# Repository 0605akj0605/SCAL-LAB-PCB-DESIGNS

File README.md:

# SCAL LAB: PCB Design and Hardware Integration– Automated Cooking Stove 

This repository contains PCB designs initially intended for an automated cooking stove project and the IoT hardware schematic for the proposed gas stove. Although the final implementation using a PCB was dropped, the repository includes schematic and board layouts for circuits designed during the exploration and learning phase.
Also, it contains the hardware   integrated schematic to act as a proof of concept for the proposed stove.

## 🔧 Tool Used

- [Autodesk EAGLE EDA](https://www.autodesk.com/products/eagle/overview)

## 🤝 Collaborators

Worked with **Naman Jain** and **Chiranjit Saha** to conceptualize and partially prototype an IoT-enabled automated gas stove. The system architecture included:

- Spark Plug  (to ignite the gas)
- Temperature Sensor (to monitor the flame temperature)
- MQ-7 gas sensor (for monitoring the flame)
- Servo Motor (to rotate the stove knob)
- NodeMCU for sending data to and from the IoT cloud service, ThingSpeak.
- Arduino MEGA for reading the sensor values and communicating the same with ESP32 over the UART protocol.

These components were to be integrated for automatic gas ignition and control based on environmental conditions.

## 🧩 Practice Circuit Schematic

One of the practice schematic designs is shown below:

 <!-- Make sure this path matches your repo file structure -->

## 🛠️ Skills Practiced

- PCB Schematic & Layout Design
- EAGLE Board Design Workflow
- IoT Hardware Integration
- Collaborative Design Planning

## 📌 Disclaimer

These PCB designs and hardware schematics are not part of a finalized or fabricated product, as the project was called off post the summer of 2024 after my internship duration.

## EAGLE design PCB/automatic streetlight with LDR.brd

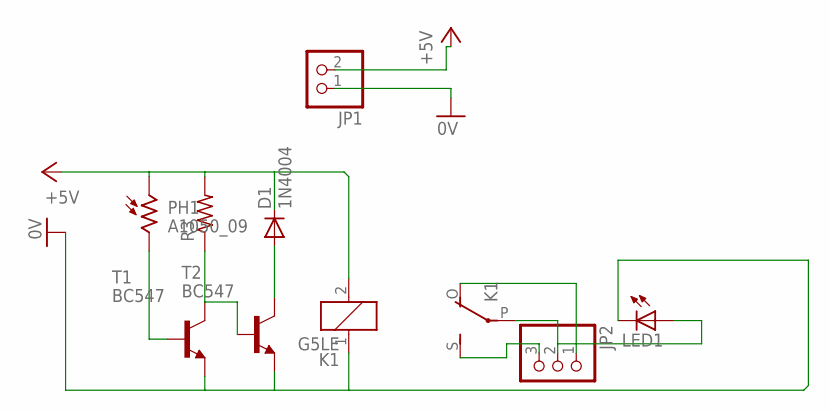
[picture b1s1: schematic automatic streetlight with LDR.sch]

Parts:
D1: 1N4004; DO41-10
JP1: PINHD-1X2; 1X02
JP2: PINHD-1X3; 1X03
K1: G5LE
LED1: LED3MM
PH1: A1050_09; T0-46-A10XX
R3: R-US_0207/10; 0207/10
T1, T2: BC547; TO92

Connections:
0V: JP1.1, K1.1, LED1.K (C), T1.1 (E), T2.1 (E)
+5V: D1.C, JP1.2, K1.2, PH1.1, R3.2
unnamed: PH1.2, T1.2 (B)
unnamed: JP2.2, K1.P, LED1.A
unnamed: JP2.1, K1.O
unnamed: JP2.3, K1.S
unnamed: R3.1, T1.3 (C), T2.2 (B)
unnamed: D1.A, T2.3 (C)

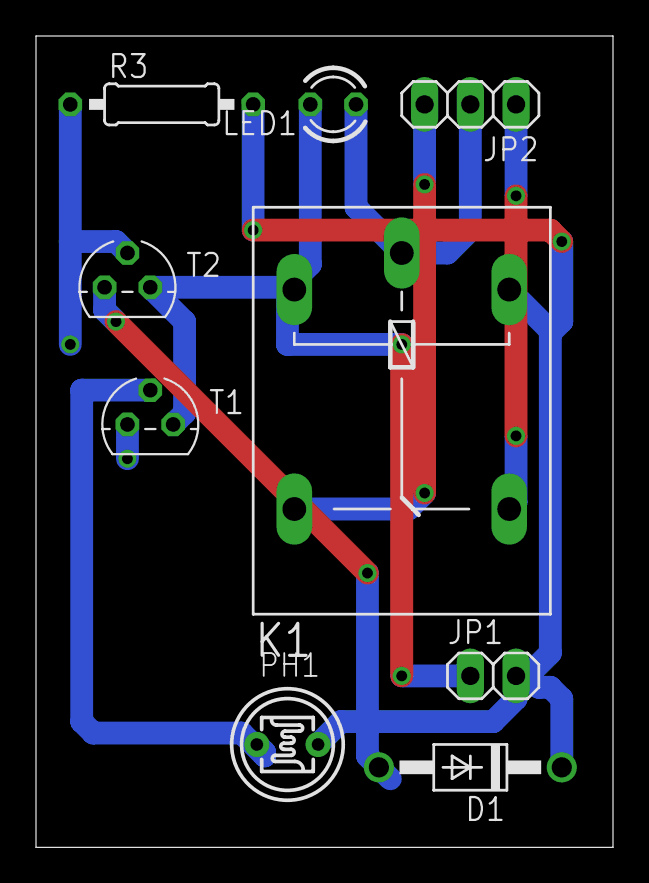
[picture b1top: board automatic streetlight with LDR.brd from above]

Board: 2 copper layers, 32.1 x 45.1 mm, 9 parts (0 on the bottom side), 8 nets.

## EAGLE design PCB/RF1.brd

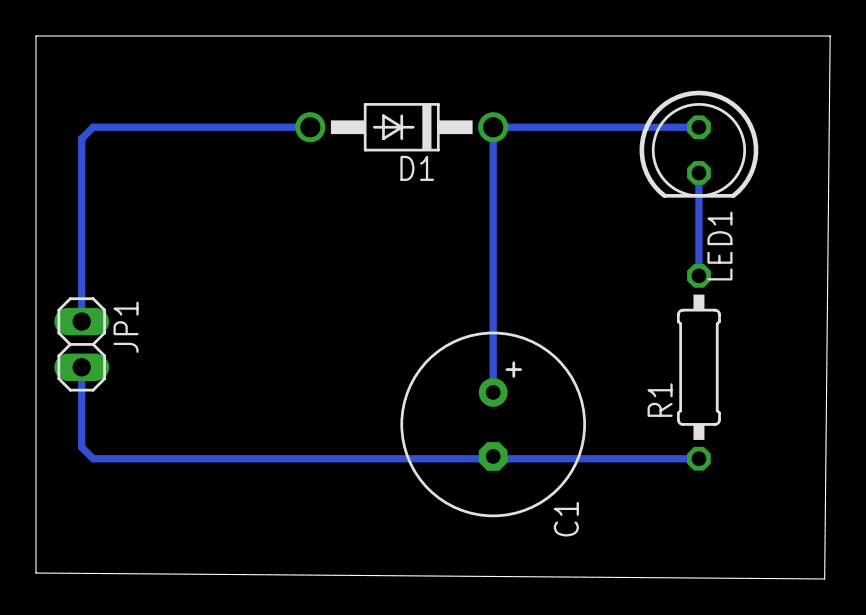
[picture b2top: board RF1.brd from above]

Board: 2 copper layers, 44.1 x 30.2 mm, 5 parts (0 on the bottom side), 4 nets.

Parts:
C1: E3,5-10
D1: 1N4004; DO41-10
JP1: 1X02
LED1: LED5MM
R1: 0207/10

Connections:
unnamed: D1.A, JP1.1
unnamed: LED1.K, R1.2
unnamed: C1.-, JP1.2, R1.1
unnamed: C1.+, D1.C, LED1.A

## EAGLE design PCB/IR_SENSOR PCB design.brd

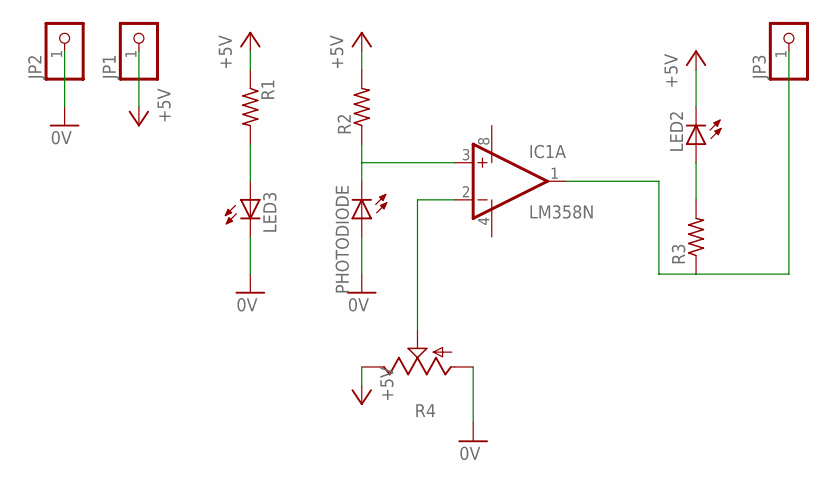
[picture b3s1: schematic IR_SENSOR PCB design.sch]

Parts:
IC1: LM358N; DIL08
JP1, JP2, JP3: PINHD-1X1; 1X01
LED2, LED3: LED3MM
PHOTODIODE: LED3MM
R1, R2, R3: R-US_0207/10; 0207/10
R4: TRIM_US-B25U; B25U

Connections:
0V: JP2.1, LED3.K (C), PHOTODIODE.A, R4.A
+5V: JP1.1, LED2.K (C), R1.1, R2.2, R4.E
unnamed: IC1.3 (+IN), PHOTODIODE.K (C), R2.1
unnamed: IC1.2 (-IN), R4.S
unnamed: LED3.A, R1.2
unnamed: LED2.A, R3.2
unnamed: IC1.1 (OUT), JP3.1, R3.1
V+: IC1.8 (V+)
V-: IC1.4 (V-)

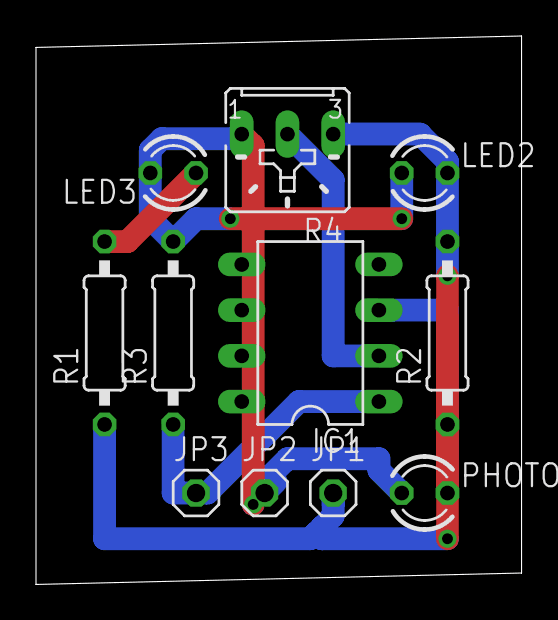
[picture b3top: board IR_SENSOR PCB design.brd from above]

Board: 2 copper layers, 27.0 x 30.5 mm, 11 parts (0 on the bottom side), 7 nets.

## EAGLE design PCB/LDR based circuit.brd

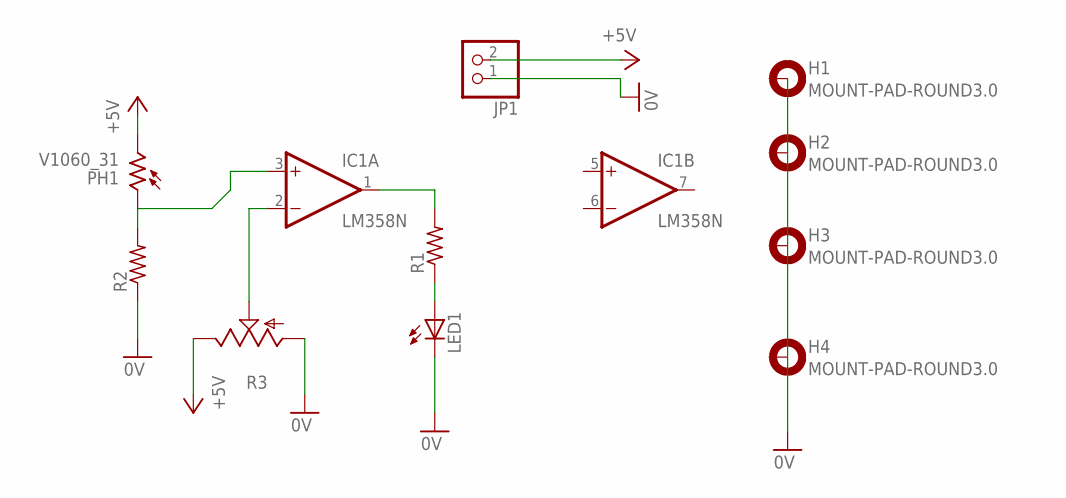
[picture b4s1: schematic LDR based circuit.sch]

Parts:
H1, H2, H3, H4: MOUNT-PAD-ROUND3.0; 3,0-PAD
IC1: LM358N; DIL08
JP1: PINHD-1X2; 1X02
LED1: LED5MM
PH1: V1060_31; TO-5_V10
R1, R2: R-US_0207/10; 0207/10
R3: TRIM_US-B25P; B25P

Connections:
0V: JP1.1, LED1.K (C), R2.1, R3.A
+5V: JP1.2, PH1.2, R3.E
unnamed: IC1.3 (+IN), PH1.1, R2.2
unnamed: IC1.1 (OUT), R1.2
unnamed: LED1.A, R1.1
unnamed: IC1.2 (-IN), R3.S
V+: IC1.8 (V+)
V-: IC1.4 (V-)

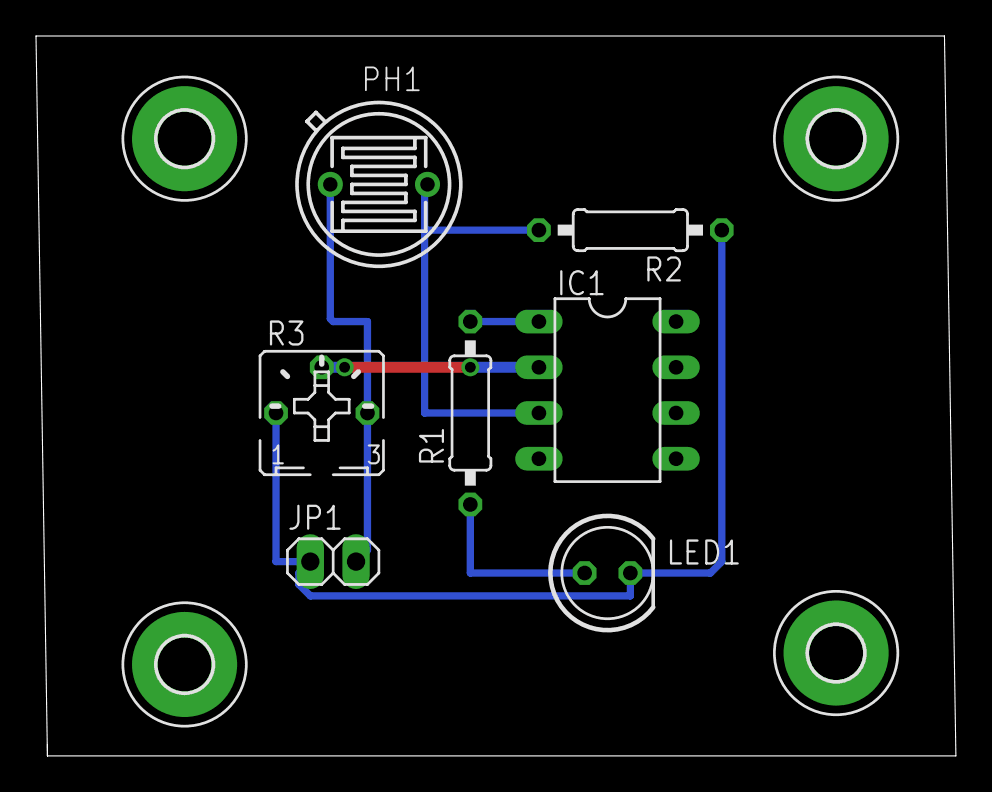
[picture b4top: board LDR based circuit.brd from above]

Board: 2 copper layers, 51.1 x 40.0 mm, 11 parts (0 on the bottom side), 6 nets.

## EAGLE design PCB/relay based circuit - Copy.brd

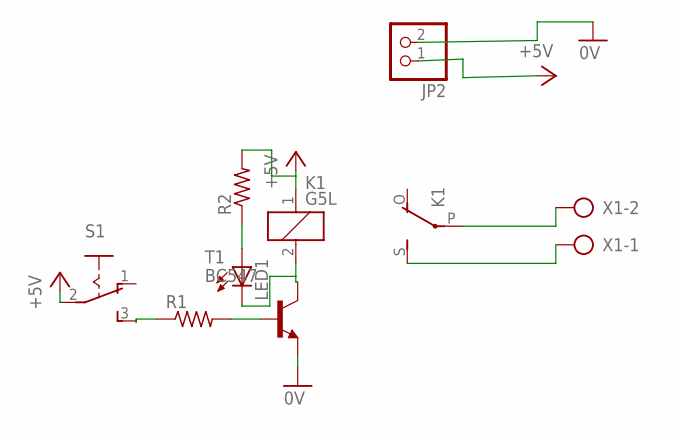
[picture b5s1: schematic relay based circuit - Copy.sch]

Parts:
JP2: PINHD-1X2; 1X02
K1: G5L; G5LE
LED1: LED3MM
R1, R2: R-US_0207/10; 0207/10
S1: M251
T1: BC547; TO92
X1: AK500/2

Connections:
0V: JP2.2, T1.1 (E)
+5V: JP2.1, K1.1, R2.2, S1.2
unnamed: R1.2, T1.2 (B)
unnamed: K1.P, X1.2
unnamed: K1.S, X1.1
unnamed: K1.2, LED1.K (C), T1.3 (C)
unnamed: R1.1, S1.3 (S)
unnamed: LED1.A, R2.1

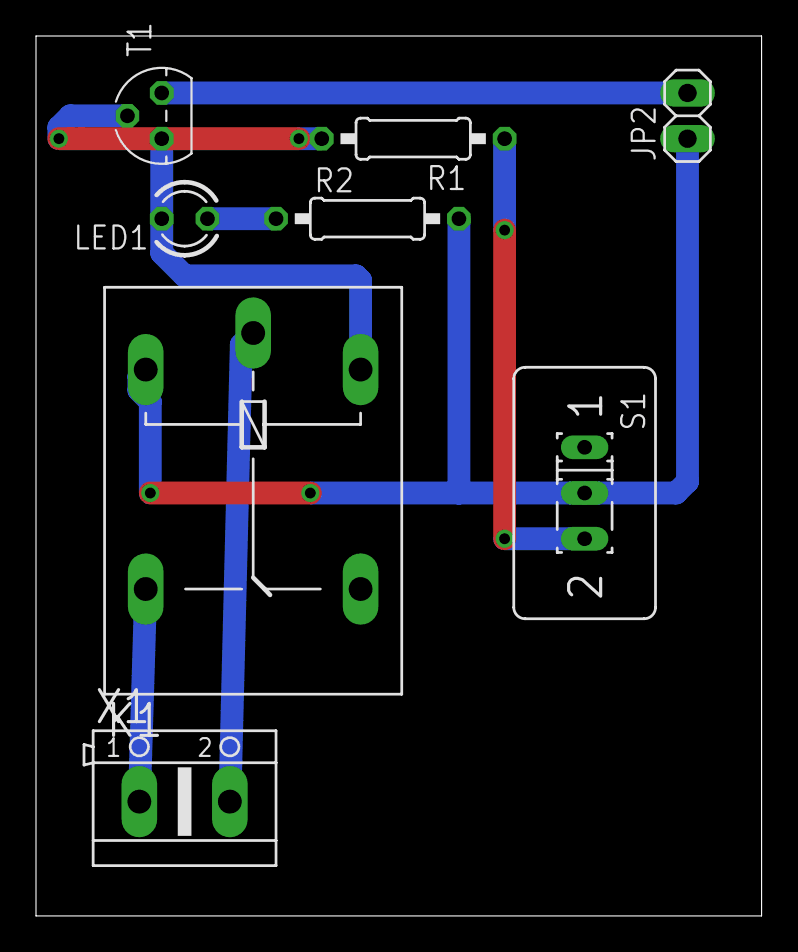
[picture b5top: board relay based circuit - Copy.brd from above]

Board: 2 copper layers, 40.3 x 48.9 mm, 8 parts (0 on the bottom side), 8 nets.

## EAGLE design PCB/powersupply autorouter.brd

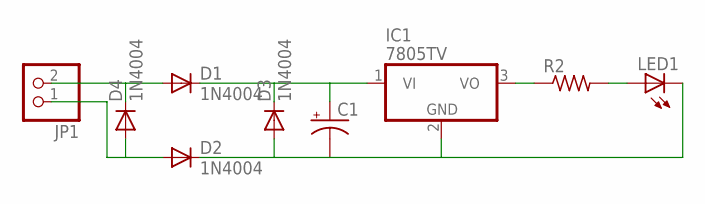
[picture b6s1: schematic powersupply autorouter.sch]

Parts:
C1: CPOL-USE3.5-10; E3,5-10
D1, D2, D3, D4: 1N4004; DO41-10
IC1: 7805TV; TO220V
JP1: PINHD-1X2; 1X02
LED1: LED3MM
R2: R-US_0207/10; 0207/10

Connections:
unnamed: C1.+, D1.C, D3.C, IC1.1 (VI)
unnamed: C1.-, D2.C, D3.A, IC1.2 (GND), LED1.K (C)
unnamed: D2.A, D4.A, JP1.1
unnamed: D1.A, D4.C, JP1.2
unnamed: LED1.A, R2.2
unnamed: IC1.3 (VO), R2.1

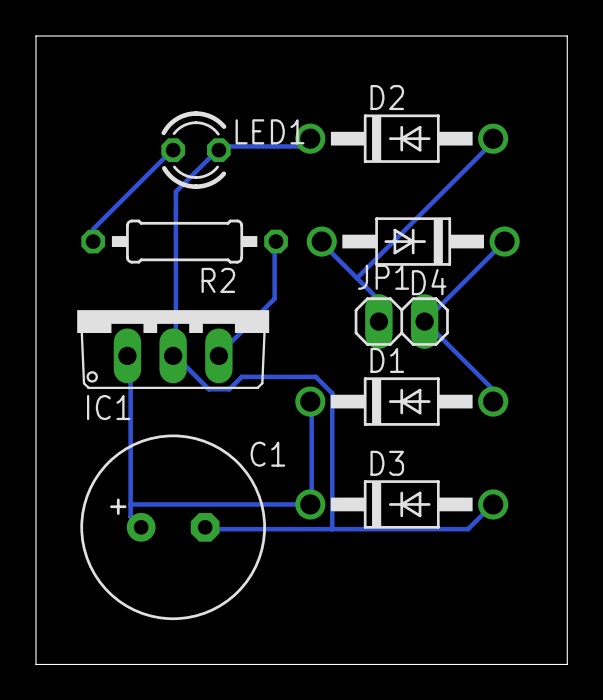
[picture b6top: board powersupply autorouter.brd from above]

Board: 2 copper layers, 29.5 x 34.9 mm, 9 parts (0 on the bottom side), 6 nets.

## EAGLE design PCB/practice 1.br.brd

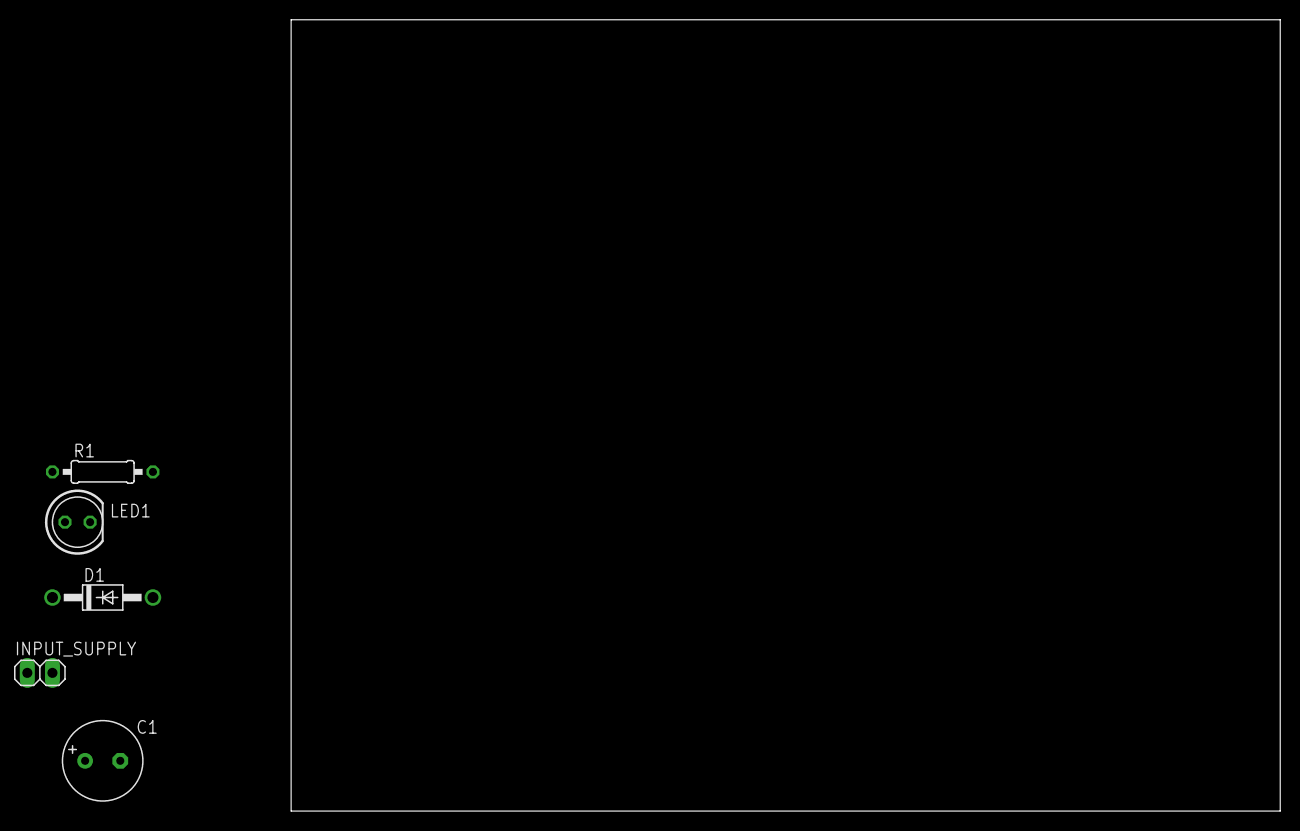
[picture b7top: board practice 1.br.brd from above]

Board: 2 copper layers, 100.0 x 80.0 mm, 5 parts (0 on the bottom side), 3 nets, no tracks yet.

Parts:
C1: 1000uf; E3,5-8
D1: 1N4004; DO41-10
INPUT_SUPPLY: 12V_AC; 1X02
LED1: LED5MM
R1: 10k; 0207/10

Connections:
12V_AC: C1.-, INPUT_SUPPLY.2, R1.1
unnamed: D1.A, INPUT_SUPPLY.1
unnamed: C1.+, D1.C, LED1.A

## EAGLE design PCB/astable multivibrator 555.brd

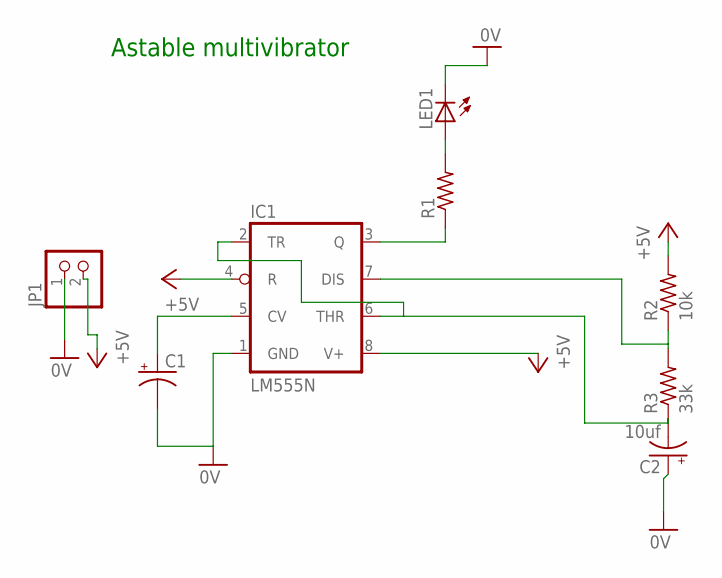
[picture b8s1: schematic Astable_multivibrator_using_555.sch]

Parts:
C1: CPOL-USE3.5-10; E3,5-10
C2: 10uf; E3,5-10
IC1: LM555N; DIL08
JP1: PINHD-1X2; 1X02
LED1: LED5MM
R1: R-US_0207/10; 0207/10
R2: 10k; 0207/10
R3: 33k; 0207/10

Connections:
0V: C1.-, C2.+, IC1.1 (GND), JP1.1, LED1.K (C)
+5V: IC1.4 (R), IC1.8 (V+), JP1.2, R2.2
unnamed: C2.-, IC1.2 (TR), IC1.6 (THR), R3.1
unnamed: LED1.A, R1.2
unnamed: IC1.3 (Q), R1.1
unnamed: C1.+, IC1.5 (CV)
unnamed: IC1.7 (DIS), R2.1, R3.2

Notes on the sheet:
Astable multivibrator

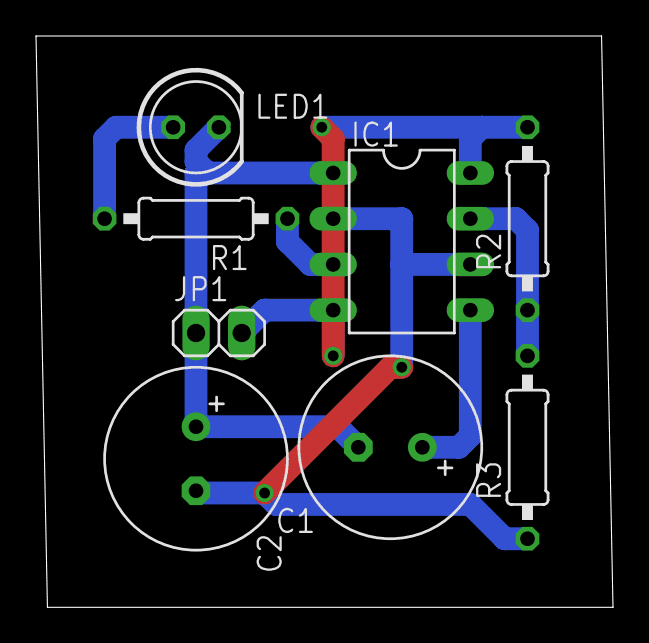
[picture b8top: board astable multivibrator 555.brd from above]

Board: 2 copper layers, 32.1 x 31.7 mm, 8 parts (0 on the bottom side), 7 nets.

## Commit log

2024-06-13 Rename automatic streetlight with LDR relay and transistor.png to automatic streetlight with LDR
